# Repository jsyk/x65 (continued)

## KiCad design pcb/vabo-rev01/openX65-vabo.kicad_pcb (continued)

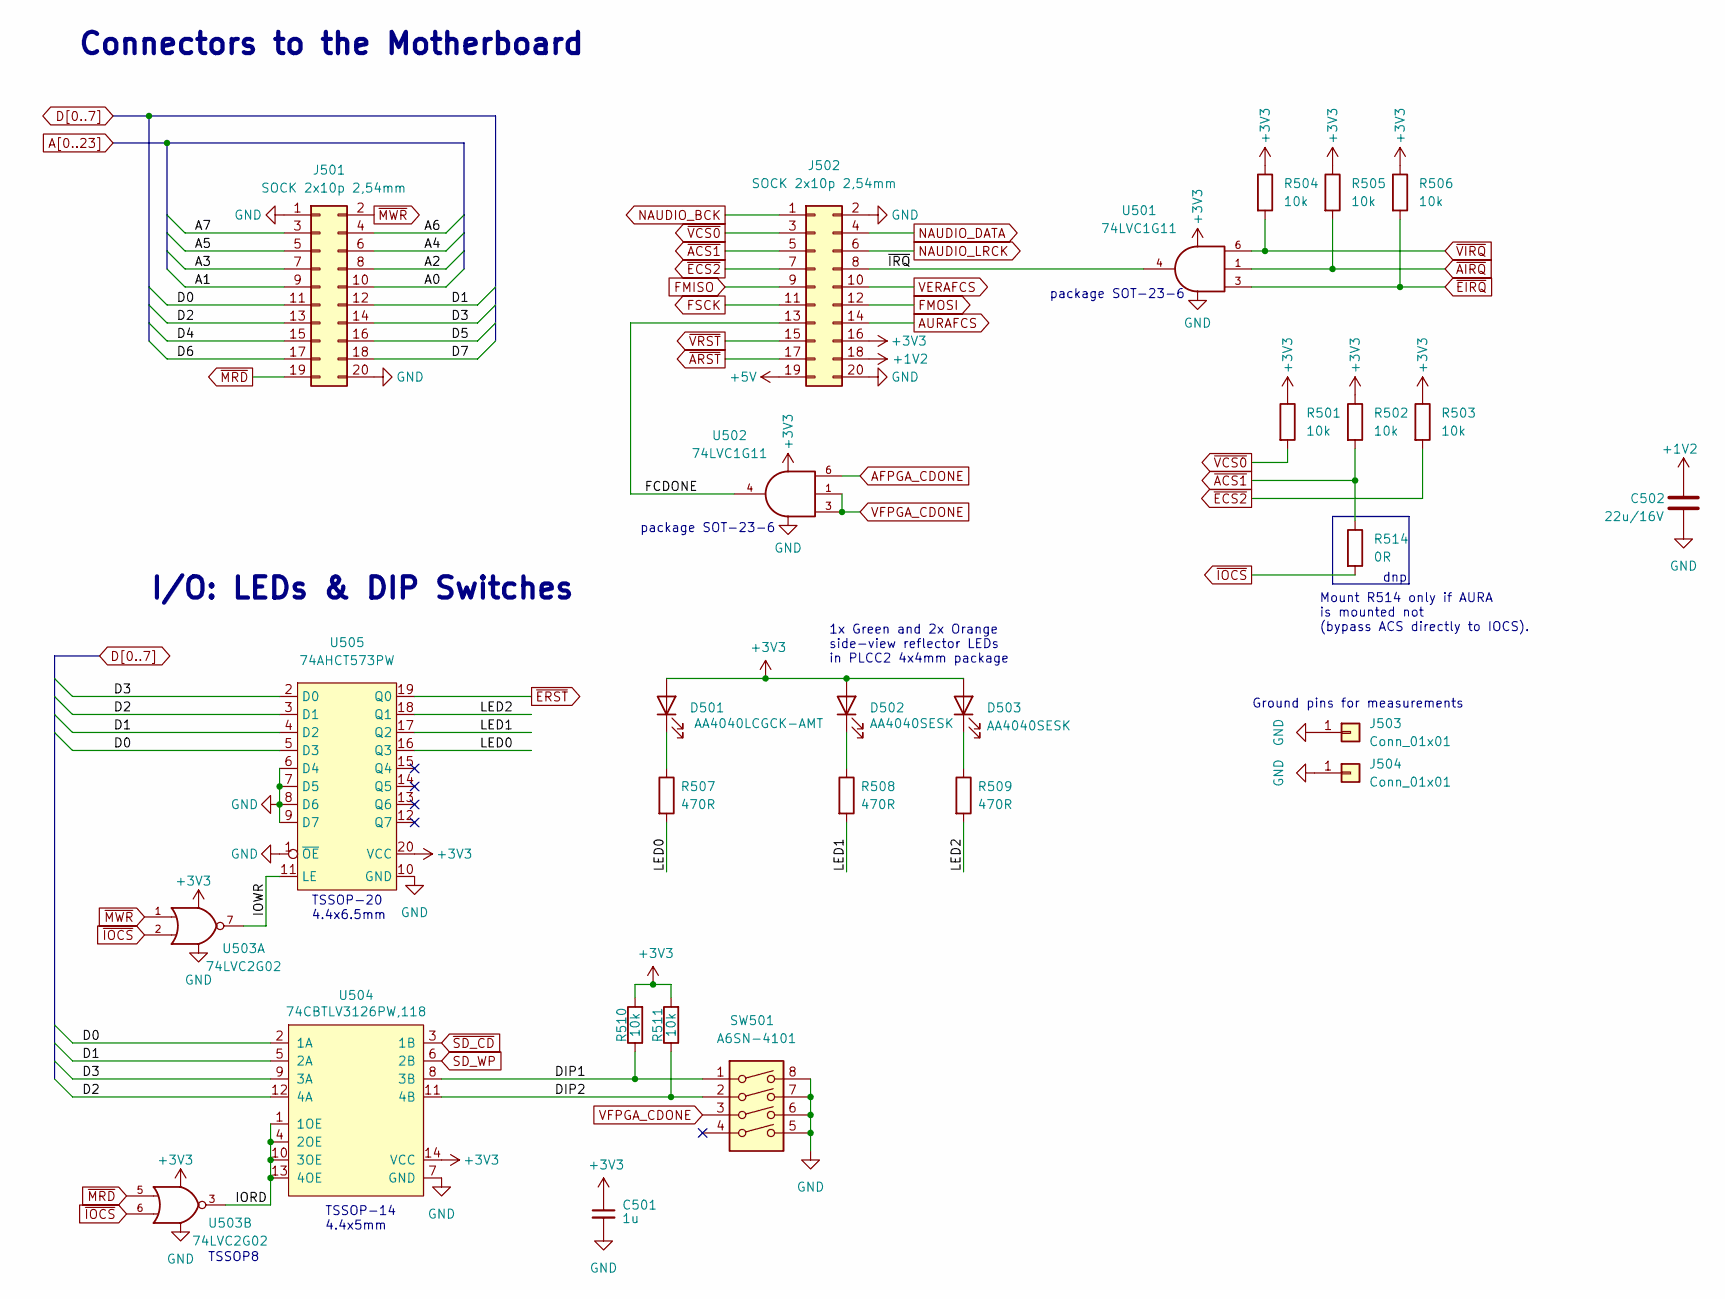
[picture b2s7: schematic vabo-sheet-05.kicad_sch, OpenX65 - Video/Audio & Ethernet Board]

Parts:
C501: 1u; C_0603_1608Metric_Pad1.08x0.95mm_HandSolder
C502: 22u/16V; C_0805_2012Metric_Pad1.18x1.45mm_HandSolder
D501: AA4040LCGCK-AMT; PLCC2_4x4mm
D502, D503: AA4040SESK; PLCC2_4x4mm
J501, J502: SOCK 2x10p 2,54mm; PinSocket_2x10_P2.54mm_Vertical
J503, J504: Conn_01x01; PinHeader_1x01_P2.54mm_Vertical
R501, R502, R503, R504, R505, R506, R510, R511: 10k; R_0603_1608Metric_Pad0.98x0.95mm_HandSolder
R507, R508, R509: 470R; R_0603_1608Metric_Pad0.98x0.95mm_HandSolder
R514: 0R; R_0603_1608Metric_Pad0.98x0.95mm_HandSolder
SW501: A6SN-4101; SW_DIP_SPSTx04_Slide_Omron_A6S-410x_W8.9mm_P2.54mm
U501, U502: 74LVC1G11; SOT-23-6_Handsoldering
U503: 74LVC2G02; TSSOP-8_3x3mm_P0.65mm
U504: 74CBTLV3126PW,118; TSSOP-14_4.4x5mm_P0.65mm
U505: 74AHCT573PW; TSSOP-20_4.4x6.5mm_P0.65mm

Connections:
+1V2: C502.2, J502.18; also elsewhere on the board
+3V3: C501.1, D501.2 (A), D502.2 (A), D503.2 (A), J502.16, R501.1, R502.1, R503.1, R504.1, R505.1, R506.1, R510.2, R511.2, U501.5 (VCC), U502.5 (VCC), U503.8 (VCC), U504.14 (VCC), U505.20 (VCC); also elsewhere on the board
+5V: J502.19; also elsewhere on the board
/Motherboard Connectors/DIP1: R510.1, SW501.1, U504.8 (3B)
/Motherboard Connectors/DIP2: R511.1, SW501.2, U504.11 (4B)
/Motherboard Connectors/FCDONE: J502.13, U502.4
/Motherboard Connectors/IORD: U503.3, U504.1 (1OE), U504.4 (2OE), U504.10 (3OE), U504.13 (4OE)
/Motherboard Connectors/IOWR: U503.7, U505.11 (LE)
/Motherboard Connectors/LED0: R507.2, U505.16 (Q3)
/Motherboard Connectors/LED1: R508.2, U505.17 (Q2)
/Motherboard Connectors/LED2: R509.2, U505.18 (Q1)
/Motherboard Connectors/~IRQ: J502.8, U501.4
A0: J501.10; also elsewhere on the board
A1: J501.9; also elsewhere on the board
A2: J501.8; also elsewhere on the board
A3: J501.7; also elsewhere on the board
A4: J501.6; also elsewhere on the board
A5: J501.5
A6: J501.4
A7: J501.3
AFPGA_CDONE: U502.6; also elsewhere on the board
AURAFCS: J502.14; also elsewhere on the board
D0: J501.11, U504.2 (1A), U505.5 (D3); also elsewhere on the board
D1: J501.12, U504.5 (2A), U505.4 (D2); also elsewhere on the board
D2: J501.13, U504.12 (4A), U505.3 (D1); also elsewhere on the board
D3: J501.14, U504.9 (3A), U505.2 (D0); also elsewhere on the board
D4: J501.15; also elsewhere on the board
D5: J501.16; also elsewhere on the board
D6: J501.17; also elsewhere on the board
D7: J501.18; also elsewhere on the board
FMISO: J502.9; also elsewhere on the board
FMOSI: J502.12; also elsewhere on the board
FSCK: J502.11; also elsewhere on the board
GND: C501.2, C502.1, J501.1, J501.20, J502.2, J502.20, J503.1, J504.1, SW501.5, SW501.6, SW501.7, SW501.8, U501.2 (GND), U502.2 (GND), U503.4 (GND), U504.7 (GND), U505.1 (~OE), U505.6 (D4), U505.7 (D5), U505.8 (D6), U505.9 (D7), U505.10 (GND); also elsewhere on the board
NAUDIO_BCK: J502.1; also elsewhere on the board
NAUDIO_DATA: J502.4; also elsewhere on the board
NAUDIO_LRCK: J502.6; also elsewhere on the board
unnamed: D501.1 (K), R507.1
unnamed: D502.1 (K), R508.1
unnamed: D503.1 (K), R509.1
SD_WP: U504.6 (2B); also elsewhere on the board
VERAFCS: J502.10; also elsewhere on the board
VFPGA_CDONE: SW501.3, U502.1, U502.3; also elsewhere on the board
~ACS1: J502.5, R502.2, R514.1; also elsewhere on the board
~AIRQ: R505.2, U501.1; also elsewhere on the board
~ARST: J502.17; also elsewhere on the board
~ECS2: J502.7, R503.2; also elsewhere on the board
~EIRQ: R506.2, U501.3; also elsewhere on the board
~ERST: U505.19 (Q0); also elsewhere on the board
~IOCS: R514.2, U503.2, U503.6; also elsewhere on the board
~MRD: J501.19, U503.5; also elsewhere on the board
~MWR: J501.2, U503.1; also elsewhere on the board
~SD_CD: U504.3 (1B); also elsewhere on the board
~VCS0: J502.3, R501.2; also elsewhere on the board
~VIRQ: R504.2, U501.6; also elsewhere on the board
~VRST: J502.15; also elsewhere on the board

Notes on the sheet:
package SOT-23-6
Ground pins for measurements
TSSOP8
Mount R514 only if AURA is mounted not (bypass ACS directly to IOCS).
dnp
TSSOP-14 4.4x5mm
TSSOP-20 4.4x6.5mm
1x Green and 2x Orange side-view reflector LEDs in PLCC2 4x4mm package
Connectors to the Motherboard
I/O: LEDs & DIP Switches

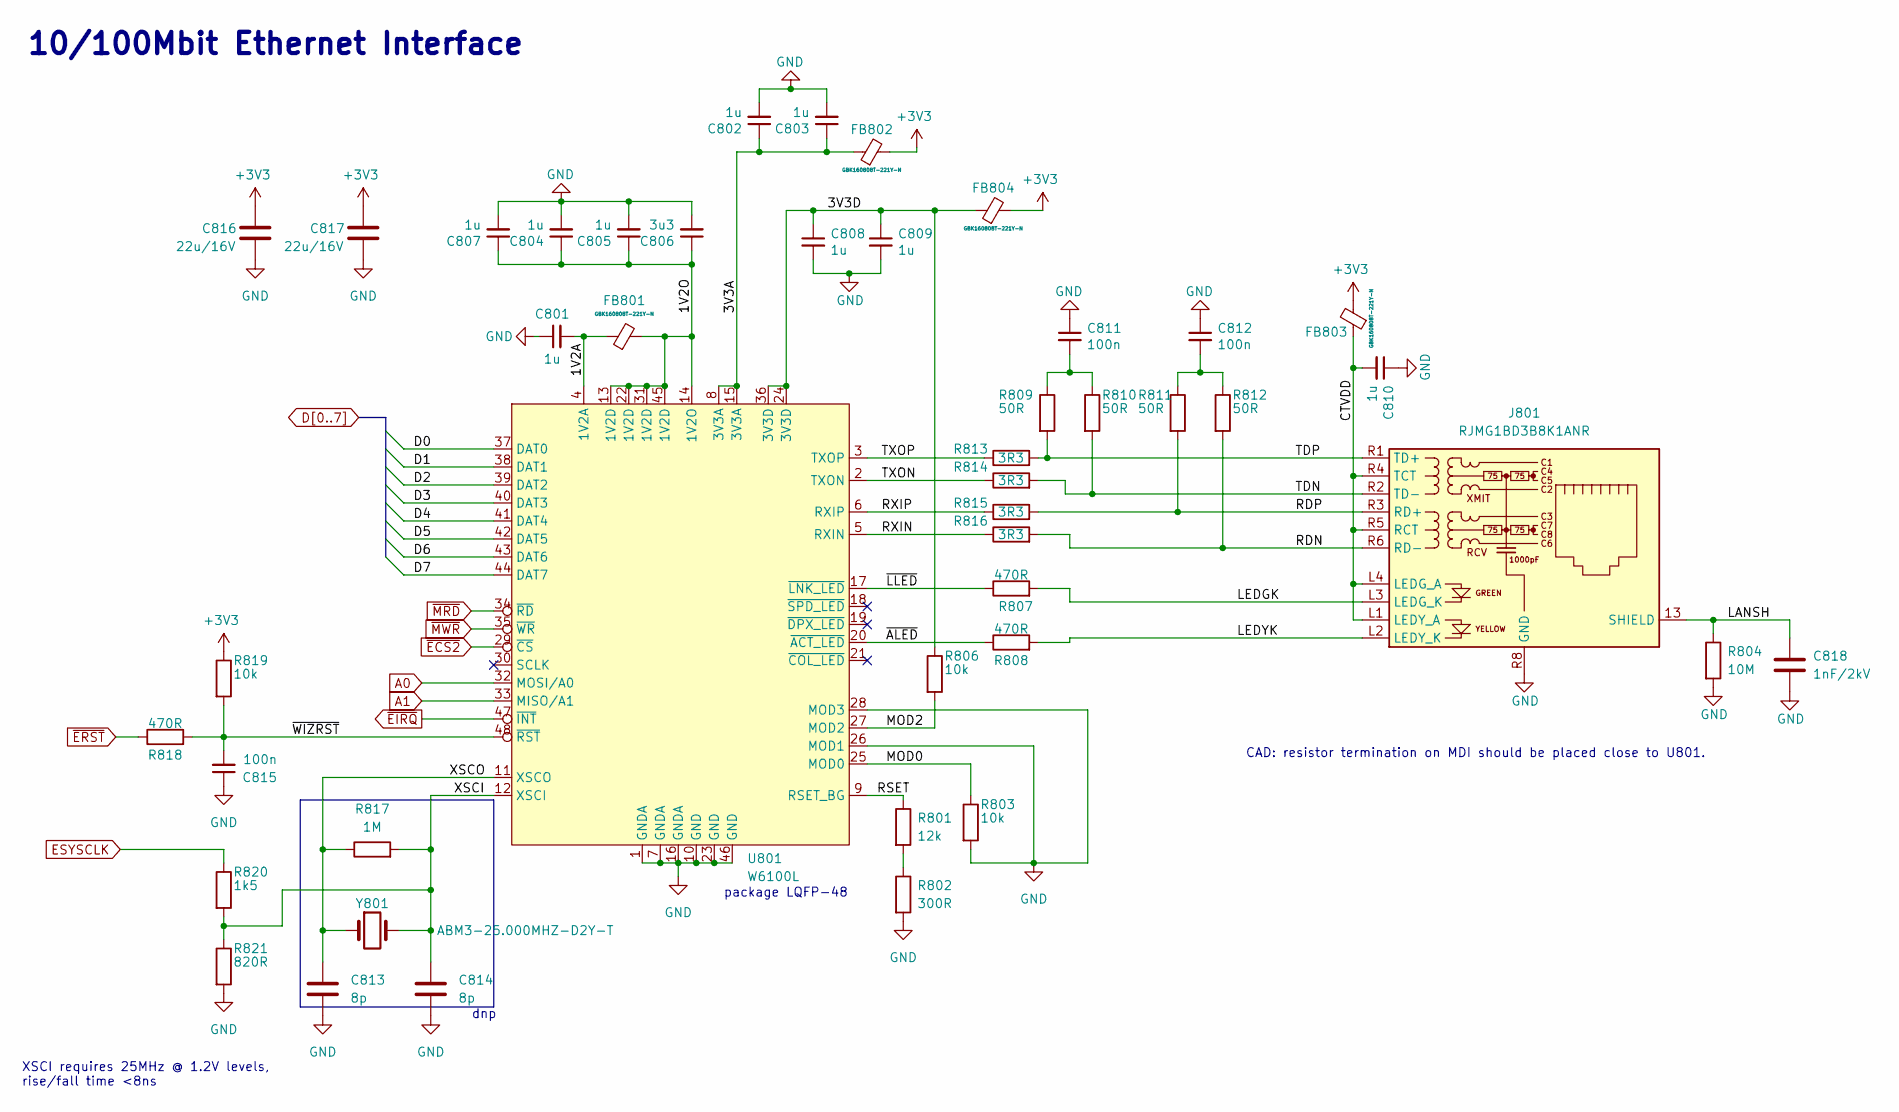
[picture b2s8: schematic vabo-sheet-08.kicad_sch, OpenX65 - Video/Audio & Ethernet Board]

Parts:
C801, C802, C803, C804, C805, C807, C808, C809, C810: 1u; C_0603_1608Metric_Pad1.08x0.95mm_HandSolder
C806: 3u3; C_0603_1608Metric_Pad1.08x0.95mm_HandSolder
C811, C812, C815: 100n; C_0603_1608Metric_Pad1.08x0.95mm_HandSolder
C813, C814: 8p; C_0603_1608Metric_Pad1.08x0.95mm_HandSolder
C816, C817: 22u/16V; C_0805_2012Metric_Pad1.18x1.45mm_HandSolder
C818: 1nF/2kV; C_1206_3216Metric_Pad1.33x1.80mm_HandSolder
FB801, FB802, FB803, FB804: GBK160808T-221Y-N; R_0603_1608Metric_Pad0.98x0.95mm_HandSolder
J801: RJMG1BD3B8K1ANR; RJ45_Amphenol_RJMG1BD3B8K1ANR
R801: 12k; R_0603_1608Metric_Pad0.98x0.95mm_HandSolder
R802: 300R; R_0603_1608Metric_Pad0.98x0.95mm_HandSolder
R803, R806, R819: 10k; R_0603_1608Metric_Pad0.98x0.95mm_HandSolder
R804: 10M; R_2512_6332Metric_Pad1.40x3.35mm_HandSolder
R807, R808, R818: 470R; R_0603_1608Metric_Pad0.98x0.95mm_HandSolder
R809, R810, R811, R812: 50R; R_0603_1608Metric_Pad0.98x0.95mm_HandSolder
R813, R814, R815, R816: 3R3; R_0603_1608Metric_Pad0.98x0.95mm_HandSolder
R817: 1M; R_0603_1608Metric_Pad0.98x0.95mm_HandSolder
R820: 1k5; R_0603_1608Metric_Pad0.98x0.95mm_HandSolder
R821: 820R; R_0603_1608Metric_Pad0.98x0.95mm_HandSolder
U801: W6100L; LQFP-48_7x7mm_P0.5mm
Y801: ABM3-25.000MHZ-D2Y-T; Crystal_SMD_Abracon_ABM3-2Pin_5.0x3.2mm_HandSoldering

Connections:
+3V3: C816.2, C817.2, FB802.2, FB803.2, FB804.2, R819.1; also elsewhere on the board
/Ethernet/1V2A: C801.2, FB801.1, U801.4 (1V2A)
/Ethernet/1V2O: C804.1, C805.1, C806.1, C807.1, FB801.2, U801.13 (1V2D), U801.14 (1V2O), U801.22 (1V2D), U801.31 (1V2D), U801.45 (1V2D)
/Ethernet/3V3A: C802.1, C803.1, FB802.1, U801.8 (3V3A), U801.15 (3V3A)
/Ethernet/3V3D: C808.1, C809.1, FB804.1, R806.1, U801.24 (3V3D), U801.36 (3V3D)
/Ethernet/CTVDD: C810.2, FB803.1, J801.L1 (LEDY_A), J801.L4 (LEDG_A), J801.R4 (TCT), J801.R5 (RCT)
/Ethernet/LANSH: C818.1, J801.13 (SHIELD), R804.1
/Ethernet/LEDGK: J801.L3 (LEDG_K), R807.2
/Ethernet/LEDYK: J801.L2 (LEDY_K), R808.2
/Ethernet/MOD0: R803.1, U801.25 (MOD0)
/Ethernet/MOD2: R806.2, U801.27 (MOD2)
/Ethernet/RDN: J801.R6 (RD-), R812.2, R816.2
/Ethernet/RDP: J801.R3 (RD+), R811.2, R815.2
/Ethernet/RSET: R801.1, U801.9 (RSET_BG)
/Ethernet/RXIN: R816.1, U801.5 (RXIN)
/Ethernet/RXIP: R815.1, U801.6 (RXIP)
/Ethernet/TDN: J801.R2 (TD-), R810.2, R814.2
/Ethernet/TDP: J801.R1 (TD+), R809.2, R813.2
/Ethernet/TXON: R814.1, U801.2 (TXON)
/Ethernet/TXOP: R813.1, U801.3 (TXOP)
/Ethernet/XSCI: C814.1, R817.2, R820.2, R821.1, U801.12 (XSCI), Y801.2
/Ethernet/XSCO: C813.1, R817.1, U801.11 (XSCO), Y801.1
/Ethernet/~ALED: R808.1, U801.20 (~ACT_LED)
/Ethernet/~LLED: R807.1, U801.17 (~LNK_LED)
/Ethernet/~WIZRST: C815.2, R818.2, R819.2, U801.48 (~RST)
A0: U801.32 (MOSI/A0); also elsewhere on the board
A1: U801.33 (MISO/A1); also elsewhere on the board
D0: U801.37 (DAT0); also elsewhere on the board
D1: U801.38 (DAT1); also elsewhere on the board
D2: U801.39 (DAT2); also elsewhere on the board
D3: U801.40 (DAT3); also elsewhere on the board
D4: U801.41 (DAT4); also elsewhere on the board
D5: U801.42 (DAT5); also elsewhere on the board
D6: U801.43 (DAT6); also elsewhere on the board
D7: U801.44 (DAT7); also elsewhere on the board
ESYSCLK: R820.1; also elsewhere on the board
GND: C801.1, C802.2, C803.2, C804.2, C805.2, C806.2, C807.2, C808.2, C809.2, C810.1, C811.1, C812.1, C813.2, C814.2, C815.1, C816.1, C817.1, C818.2, J801.R8 (GND), R802.2, R803.2, R804.2, R821.2, U801.1 (GNDA), U801.7 (GNDA), U801.10 (GND), U801.16 (GNDA), U801.23 (GND), U801.26 (MOD1), U801.28 (MOD3), U801.46 (GND); also elsewhere on the board
unnamed: C811.2, R809.1, R810.1
unnamed: C812.2, R811.1, R812.1
unnamed: R801.2, R802.1
~ECS2: U801.29 (~CS); also elsewhere on the board
~EIRQ: U801.47 (~INT); also elsewhere on the board
~ERST: R818.1; also elsewhere on the board
~MRD: U801.34 (~RD); also elsewhere on the board
~MWR: U801.35 (~WR); also elsewhere on the board

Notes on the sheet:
dnp
package LQFP-48
CAD: resistor termination on MDI should be placed close to U801.
XSCI requires 25MHz @ 1.2V levels, rise/fall time <8ns
10/100Mbit Ethernet Interface

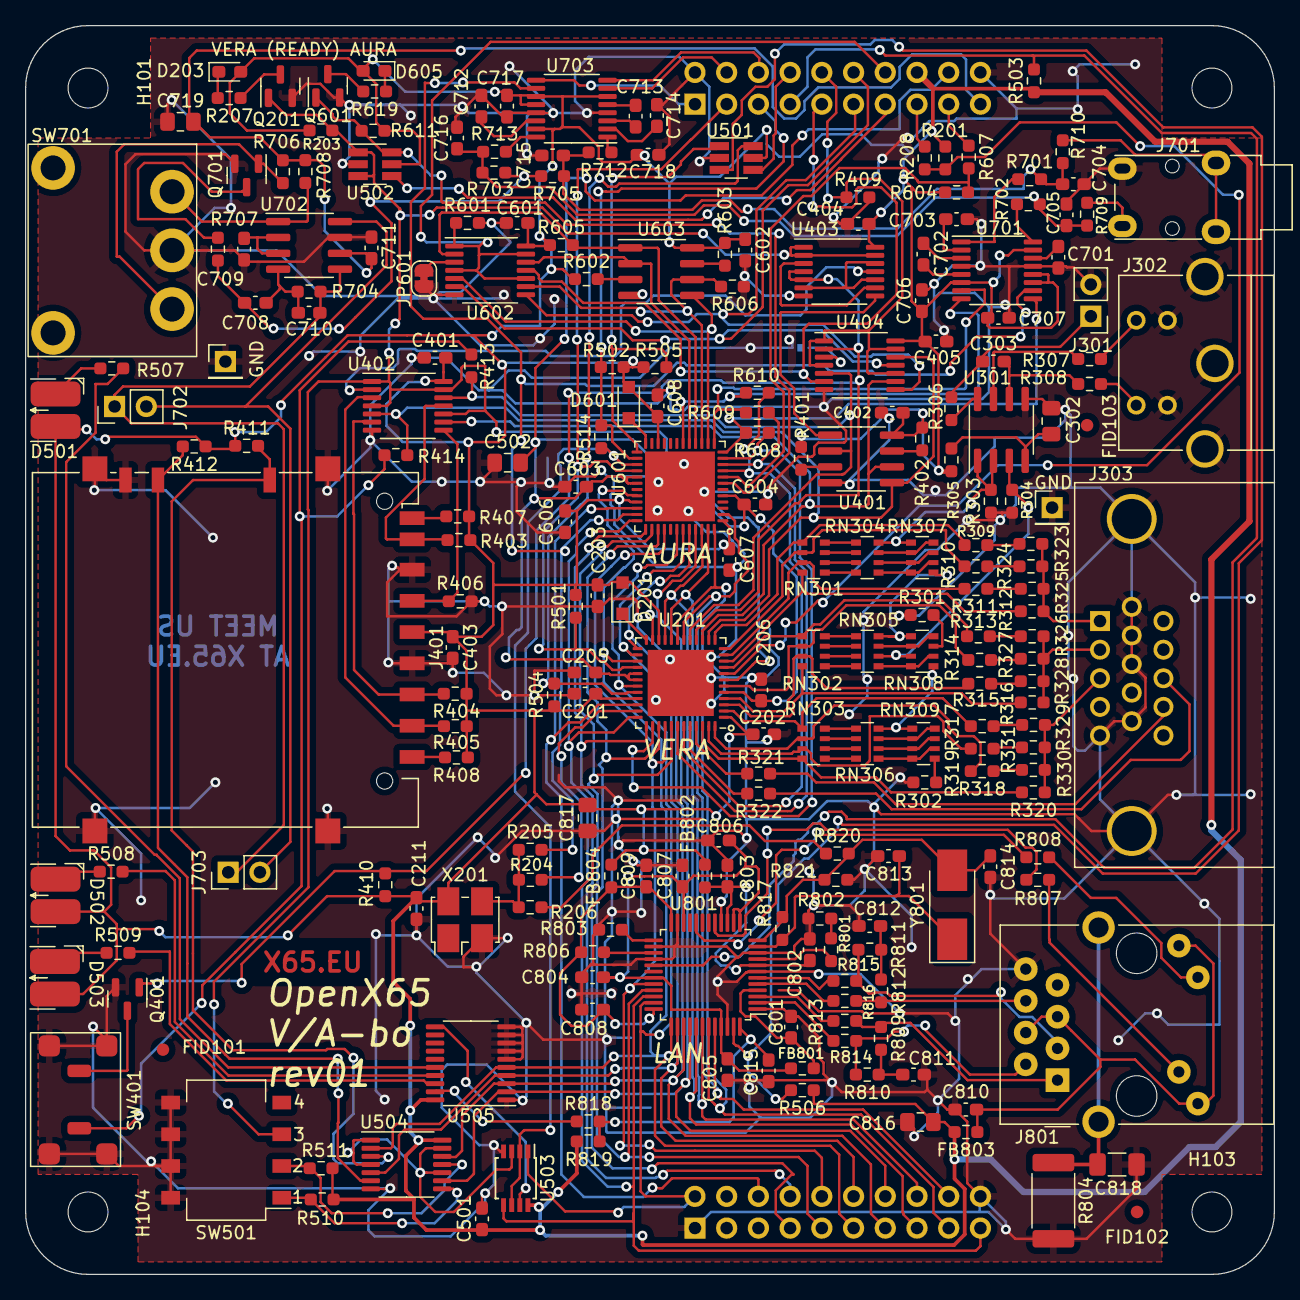
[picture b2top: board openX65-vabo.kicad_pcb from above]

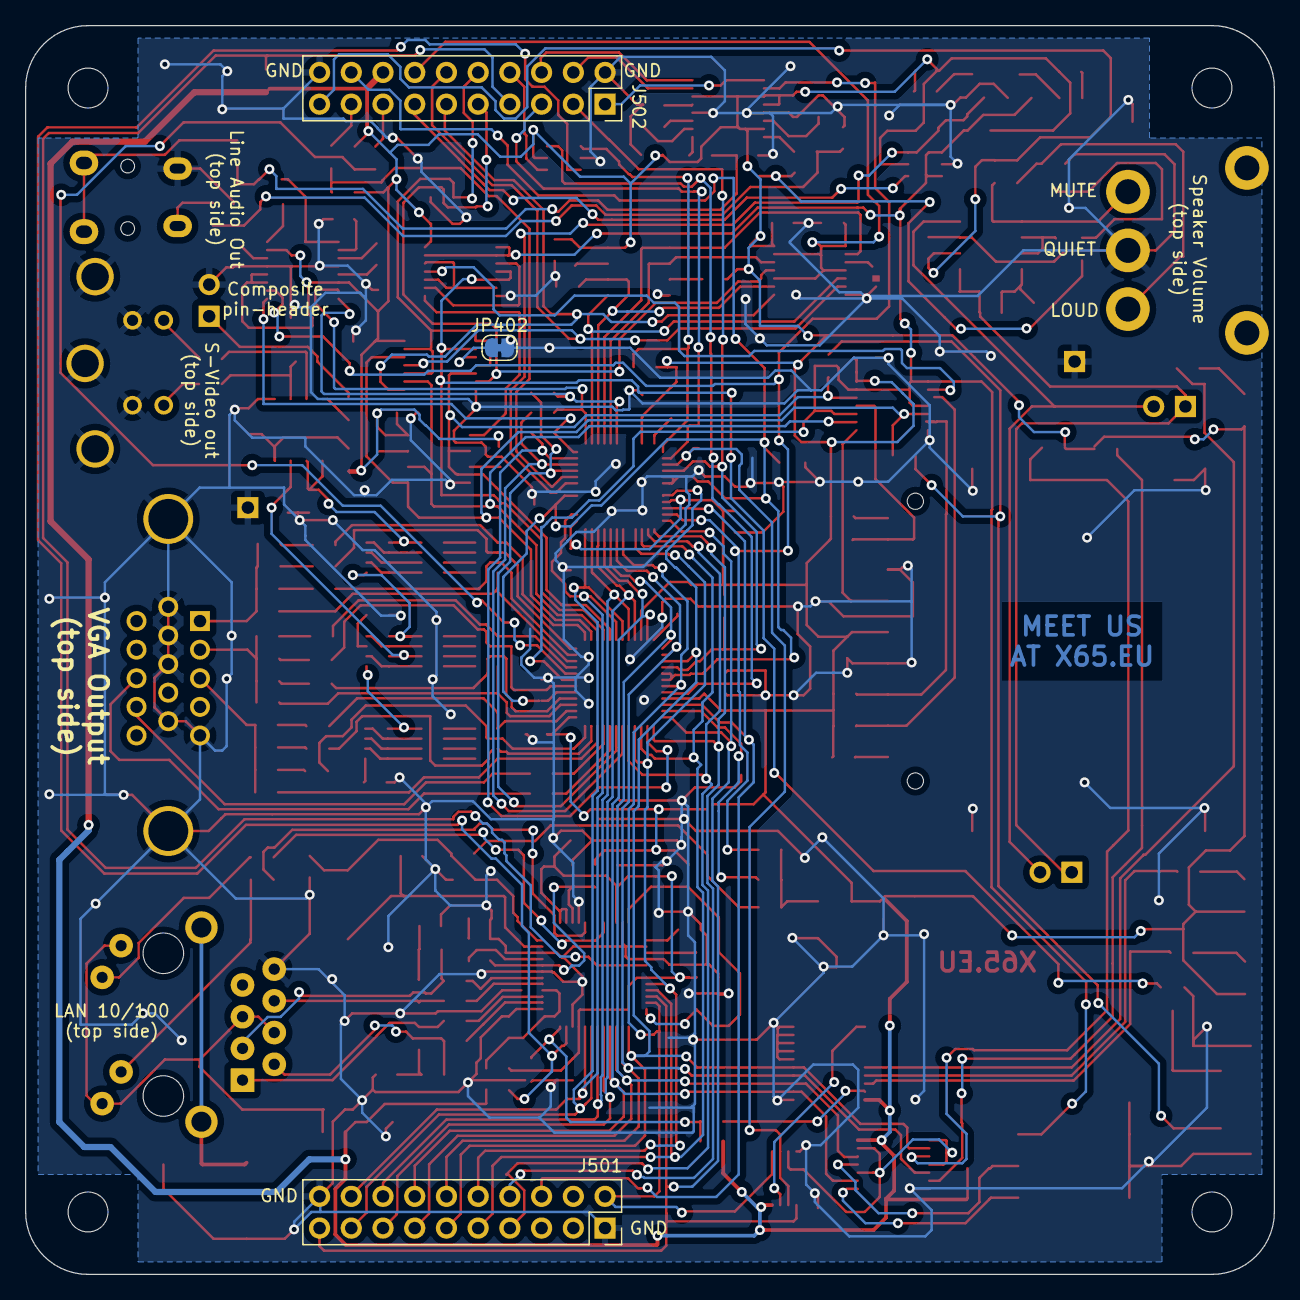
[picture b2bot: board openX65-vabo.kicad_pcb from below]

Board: 2 copper layers, 100.0 x 100.0 mm, 235 parts (3 on the bottom side), 209 nets.

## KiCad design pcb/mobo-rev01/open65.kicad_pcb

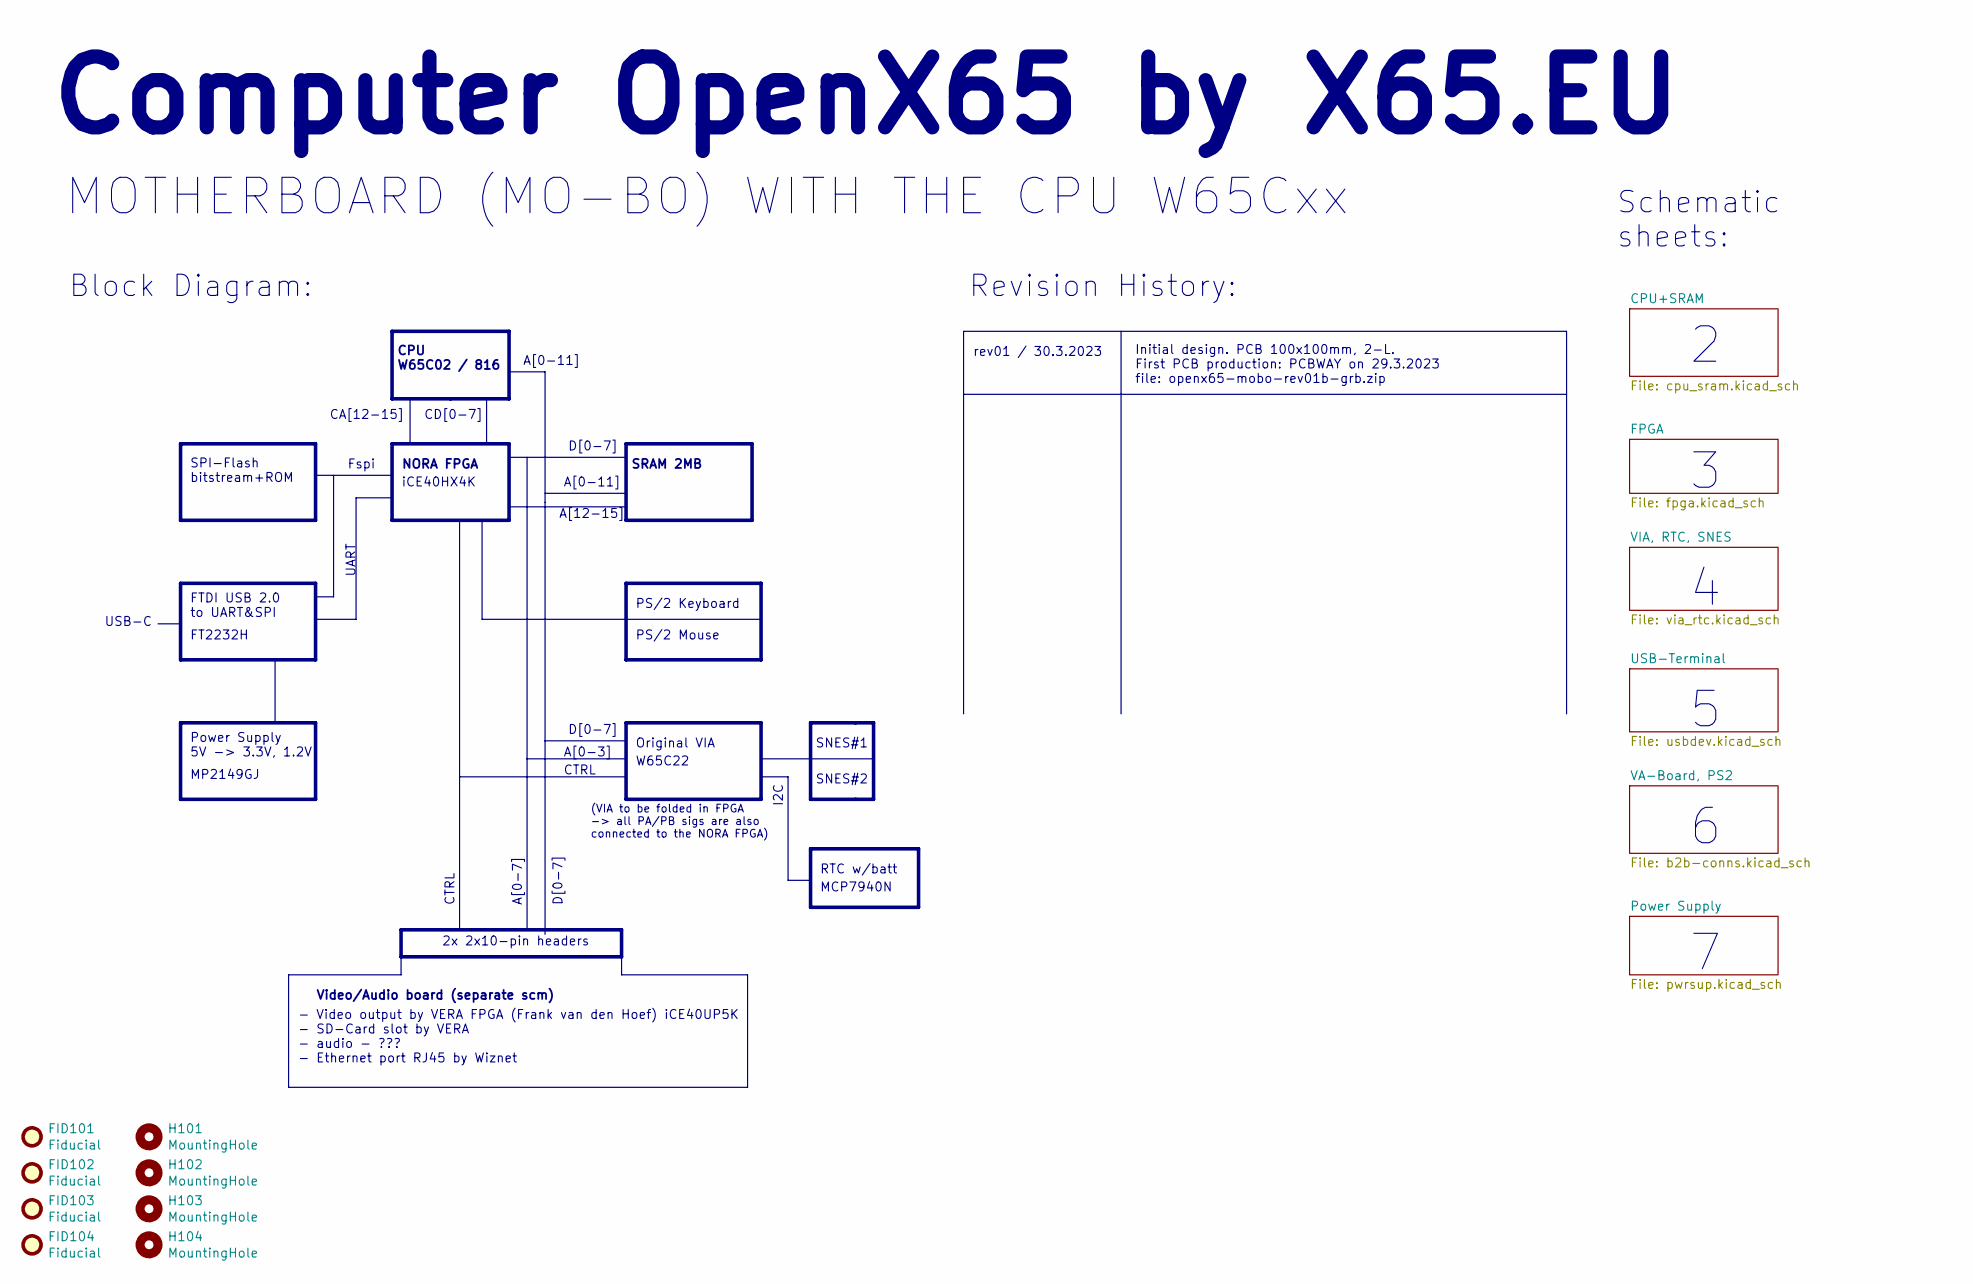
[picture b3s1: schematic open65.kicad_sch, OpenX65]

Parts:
FID101, FID102, FID103, FID104: Fiducial; Fiducial_1mm_Mask2mm
H101, H102, H103, H104: MountingHole; MountingHole_3.2mm_M3

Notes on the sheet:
Block Diagram:
CTRL
Initial design. PCB 100x100mm, 2-L. First PCB production: PCBWAY on 29.3.2023 file: openx65-mobo-rev01b-grb.zip
Schematic sheets:
MCP7940N
CA[12-15]
(VIA to be folded in FPGA -> all PA/PB sigs are also connected to the NORA FPGA)
CPU W65C02 / 816
A[12-15]
- Video output by VERA FPGA (Frank van den Hoef) iCE40UP5K - SD-Card slot by VERA - audio - ??? - Ethernet port RJ45 by Wiznet
MOTHERBOARD (MO-BO) WITH THE CPU W65Cxx
A[0-3]
Original VIA
A[0-11]
CD[0-7]
SNES#2
FT2232H
NORA FPGA
Fspi
Computer OpenX65 by X65.EU
Video/Audio board (separate scm)
Revision History:
PS/2 Keyboard
W65C22
rev01 / 30.3.2023
I2C
UART
D[0-7]
iCE40HX4K
2x 2x10-pin headers
Power Supply 5V -> 3.3V, 1.2V
SPI-Flash bitstream+ROM
MP2149GJ
RTC w/batt
USB-C
FTDI USB 2.0 to UART&SPI
PS/2 Mouse
SNES#1
A[0-7]
SRAM 2MB
